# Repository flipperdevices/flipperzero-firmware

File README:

# About
This project is used to develop applications for stm32 - ST's ARM Cortex-M3(4) MCUs, using cmake, GCC, newlib (libc), STM32CubeMX package or ChibiOS.

Requirements:
* cmake >= 2.8
* GCC toolchain with newlib (optionally).
* STM32CubeMX package for STM32F1 or STM32F4 families.
Project contains:
* CMake common toolchain file, that configures cmake to use arm toolchain.
* CMake family-specific toolchain file, that configures family-specific parameters.
* CMake modules to find and configure CMSIS ans STM32HAL components.
* CMake modules to find and configure ChibiOS components.
* CMake project template.
* Example projects:
  * stm32-blinky - blink LED using timers and PWM.
  * stm32-newlib - show date using uart and libc functions from newlib
  * stm32-chibios - blink led using ChibiOS/NIL

# Usage
First of all you need to configure toolchain and libraries, you can do this by editing gcc_stm32.cmake or (better way) pass it throught command line.
Variables for toolchain:
* TOOLCHAIN_PREFIX - where toolchain is located, **default**: /usr
* TARGET_TRIPLET - toolchain target triplet, **default**: arm-none-eabi
* STM32_CHIP - STM32 device code, e.g. STM32F407VG or STM32F103VG
* STM32_FAMILY - STM32 family (F0, F1, F4, etc.) currently, F1 and F4 family are supported. **Note:** If STM32_CHIP variable is set, STM32_FAMILY is optional.
* STM32Cube_DIR - path to STM32CubeMX directory **default**: /opt/STM32Cube_FW_F1_V1.1.0 /opt/STM32Cube_FW_F4_V1.6.0

For using scripts you'll need to copy contents of cmake folder into cmake's modules path, or use CMAKE_MODULE_PATH variable. 
Template project can be found in stm32-template folder.

## Configure
Common usage:

 ```cmake -DSTM32_CHIP=<chip> -DCMAKE_TOOLCHAIN_FILE=<path_to_gcc_stm32.cmake> -DCMAKE_BUILD_TYPE=Debug <path_to_source_dir>```

Where <chip> - stm32 chip name (e.g. STM32F100C8, STM32F407IG). 
This command will generate Makefile for project.
Scripts will try to detected chip parameters (type, flash/ram size) from chip name. 
You can set this parameters directly using following cmake variables:
* STM32_CHIP_TYPE - family-depended chip type. Global variable STM32_CHIP_TYPES contains list of valid types for current family
* STM32_FLASH_SIZE - chip flash size (e.g. 64K)
* STM32_RAM_SIZE - chip RAM size (e.g. 4K)

For using with Eclipse CDT:

 ```cmake -DSTM32_CHIP=<chip> -DCMAKE_TOOLCHAIN_FILE=<path_to_gcc_stm32.cmake> -DCMAKE_BUILD_TYPE=Debug -G "Eclipse CDT4 - Unix Makefiles" <path_to_source_dir>```

For release build:

 ```cmake -DSTM32_CHIP=<chip> -DCMAKE_TOOLCHAIN_FILE=<path_to_gcc_stm32.cmake> -DCMAKE_BUILD_TYPE=Release <path_to_source_dir>```

## Build

 ```make`
 
To build .hex:

 ```make <project name>.hex```
 
or .bin:

 ```make <project name>.bin```

## Linker script variables
Next cmake variables are useful for linker tuning:
* STM32_LINKER_SCRIPT - Path to custom linker script. You can use cmake variables (listed below) in itd.
* STM32_FLASH_ORIGIN - Start address of flash (**default**: 0x08000000)
* STM32_RAM_ORIGIN - Start address of RAM (**default**: 0x20000000)
* STM32_CCRAM_ORIGIN - Start address of Core-Coupled RAM (only for F4 family) (**default**: 0x10000000)
* STM32_FLASH_SIZE - Flash size (**default**: from chip name)
* STM32_RAM_SIZE - RAM size (**default**: from chip name)
* STM32_CCRAM_SIZE - Core-Coupled RAM size (only for F4 family) (**default**: 64 KiB)
* STM32_MIN_STACK_SIZE - Minimum stack size for error detection at link-time (**default**: 512 bytes)
* STM32_MIN_HEAP_SIZE - Minimum heap size for error detection at link-time (**default**: 0 bytes)

## Useful cmake macros
* STM32_GET_CHIP_TYPE(CHIP CHIP_TYPE) - gets chip type from chip name.
* STM32_GET_CHIP_PARAMETERS(CHIP FLASH_SIZE RAM_SIZE) - gets chip ram/flash size from chip name.
* STM32_SET_CHIP_DEFINITIONS(TARGET CHIP_TYPE) - sets chip family and type-specific compiler flags for target.
* STM32_SET_FLASH_PARAMS(TARGET ...) - sets chip flash/ram parameters for targer.
* STM32_SET_TARGET_PROPERTIES(TARGET) - sets all needed parameters and compiler flags for target. 
* STM32_GENERATE_LIBRARIES(NAME SOURCES LIBRARIES) - generates libraries for all chip types in family. Resulting libraries stored in LIBRARIES and have names in ${NAME}_${FAMILY}_${CHIP_TYPE} format.

## ChibiOS Support
This projects also supports ChibiOS v3.x.x (both nil and rt kernels). 
CMake modules for ChibiOS can find specified ChibiOS components using COMPONENTS directive. 
See project stm32-chibios for example usage.

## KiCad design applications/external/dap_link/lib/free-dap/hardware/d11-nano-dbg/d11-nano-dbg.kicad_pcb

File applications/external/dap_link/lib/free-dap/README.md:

# Free-DAP

This is a free and open implementation of the CMSIS-DAP debugger firmware.

Both SWD and JTAG protocols are supported. However JTAG was not well tested due to lack of
good targets. If you have any issues with it - let me know and I'll try to help.

## Platform requirements

To create a CMSIS-DAP compliant debugger, your platform must:
 * Implement USB HID (and raw bulk for CMSIS-DAP v2) device able to receive and send arbitrary payloads
 * Provide configuration file dap_config.h with definitions for hardware-dependent calls
 * Call dap_init() at the initialization time
 * Call dap_process_request() for every received request and send the response back

## CMSIS-DAP version support

Free-DAP library itself is protocol agnostic and implementation of the specific version
of the CMSIS-DAP protocol (v1 or v2) is up to the individual platforms.

Currently RP2040 and SAM D11 implementaitons were updated to support CMSIS-DAP v2.
Other platforms would be updated if requested or needed by me.

## Configuration

For complete list of settings see one of the existing configuration file, they are
pretty obvious.

To configure clock frequency you need to specify two parameters:
  * DAP_CONFIG_DELAY_CONSTANT - clock timing constant. This constant can be determined
    by calling dap_clock_test() with varying parameter value and measuring the frequency
    on the SWCLK pin. Delay constant value is the value of the parameter at which
    output frequency equals to 1 kHz.
  * DAP_CONFIG_FAST_CLOCK - threshold for switching to fast clock routines. This value
    defines the frequency, at which more optimal pin manipulation functions are used.
    This is the frequency produced by dap_clock_test(1) on the SWCLK pin.
    You can also measure maximum achievable frequency on your platform by calling dap_clock_test(0).

Your configuration file will need to define the following pin manipulation functions:

 * DAP_CONFIG_SWCLK_TCK_write()
 * DAP_CONFIG_SWDIO_TMS_write()
 * DAP_CONFIG_TDO_write()
 * DAP_CONFIG_nTRST_write()
 * DAP_CONFIG_nRESET_write()
 * DAP_CONFIG_SWCLK_TCK_read()
 * DAP_CONFIG_SWDIO_TMS_read()
 * DAP_CONFIG_TDI_read()
 * DAP_CONFIG_TDO_read()
 * DAP_CONFIG_nTRST_read()
 * DAP_CONFIG_nRESET_read()
 * DAP_CONFIG_SWCLK_TCK_set()
 * DAP_CONFIG_SWCLK_TCK_clr()
 * DAP_CONFIG_SWDIO_TMS_in()
 * DAP_CONFIG_SWDIO_TMS_out()

Note that all pin manipulation functions are required even if one of the interfaces (JTAG or SWD) is not enabled.

Additionally configuration file must provide basic initialization and control functions:

 * DAP_CONFIG_SETUP()
 * DAP_CONFIG_DISCONNECT()
 * DAP_CONFIG_CONNECT_SWD()
 * DAP_CONFIG_CONNECT_JTAG()
 * DAP_CONFIG_LED()
 * DAP_CONFIG_DELAY()

## Tools

A complete RP2040 build requres bin2uf2 utility to generate UF2 file suitable for the RP2040 MSC bootloader.
This utility can be downloded [here](https://github.com/ataradov/tools/tree/master/bin2uf2).

## Binaries

Generally there are no pre-built binaries due to effort required to maintain
them and low potential benefit because of custom hardware requirement.

For RP2040 and Raspberry Pi Pico board specifically there is a binary, since
it is a standard and a widely available board that has a nonvolatile bootloader.

The UF2 file is located [here](bin/free_dap_rp2040.uf2). Simply boot into
a BootROM MSC mode and copy that file to the drive.

I will try to do my best to keep this binary in sync with the code updates, but
it is a manual process, so I may forget. Let me know if you have any issues.

The pins used are as follows:

| GPIO | Function |
|:---:|:---|
| 11 | SWCLK/TCK |
| 12 | SWDIO/TMS |
| 13 | TDI |
| 14 | TDO |
| 15 | nRESET |
| 0 | VCP TX |
| 1 | VCP RX |
| 2 | VCP Status |
| 25 (LED) | DAP Status |

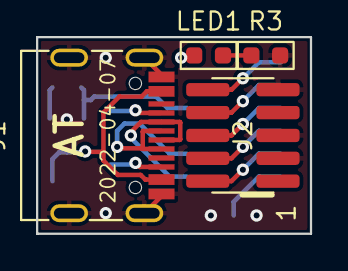
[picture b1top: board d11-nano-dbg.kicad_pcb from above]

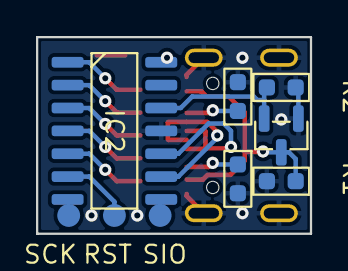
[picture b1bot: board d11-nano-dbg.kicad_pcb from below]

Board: 2 copper layers, 15.2 x 10.9 mm, 13 parts (9 on the bottom side), 17 nets.

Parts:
C1, C2: 1uF; 0603
IC1: SC662K-3.3; SOT-23
IC2: ATSAMD11C; SOIC-14
J1: USB-C
J2: Conn-5x2; Header-5x2-1.27mm-SMD
LED1: Orange; 0603
R1, R2: 5.1K; 0603
R3: 20K; 0603
TP1: SCK; TestPoint-1.27mm-SMD
TP2: RST; TestPoint-1.27mm-SMD
TP3: SIO; TestPoint-1.27mm-SMD

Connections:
+3V3: C2.2, IC1.2 (OUT), IC2.12 (VDD)
/DAP_STATUS: IC2.14 (PA4), LED1.1 (A)
/DBG_RESET: IC2.6 (PA28/RST), TP2.1
/DBG_SWCLK: IC2.7 (PA30/SCK), TP1.1
/DBG_SWDIO: IC2.8 (PA31/SIO), TP3.1
/RESET: IC2.1 (PA5), J2.10
/SWCLK/TCK: IC2.4 (PA14), J2.4
/SWDIO/TMS: IC2.5 (PA15), J2.2
/TDI: IC2.2 (PA8), J2.8
/TDO: IC2.3 (PA9), J2.6
/USB_DM: IC2.9 (PA24/DM), J1.D-1 (D-), J1.D-2 (D-)
/USB_DP: IC2.10 (PA25/DP), J1.D+1 (D+), J1.D+2 (D+)
GND: C1.1, C2.1, IC1.1 (GND), IC2.11 (GND), J1.GND1 (GND), J1.GND2 (GND), J1.S1, J1.S2, J1.S3, J1.S4, J2.3, J2.5, J2.9, R1.1, R2.1, R3.1
unnamed: J1.CC1, R2.2
unnamed: J1.CC2, R1.2
unnamed: LED1.2 (K), R3.2
VBUS: C1.2, IC1.3 (IN), J1.VBUS1 (VBUS), J1.VBUS2 (VBUS)

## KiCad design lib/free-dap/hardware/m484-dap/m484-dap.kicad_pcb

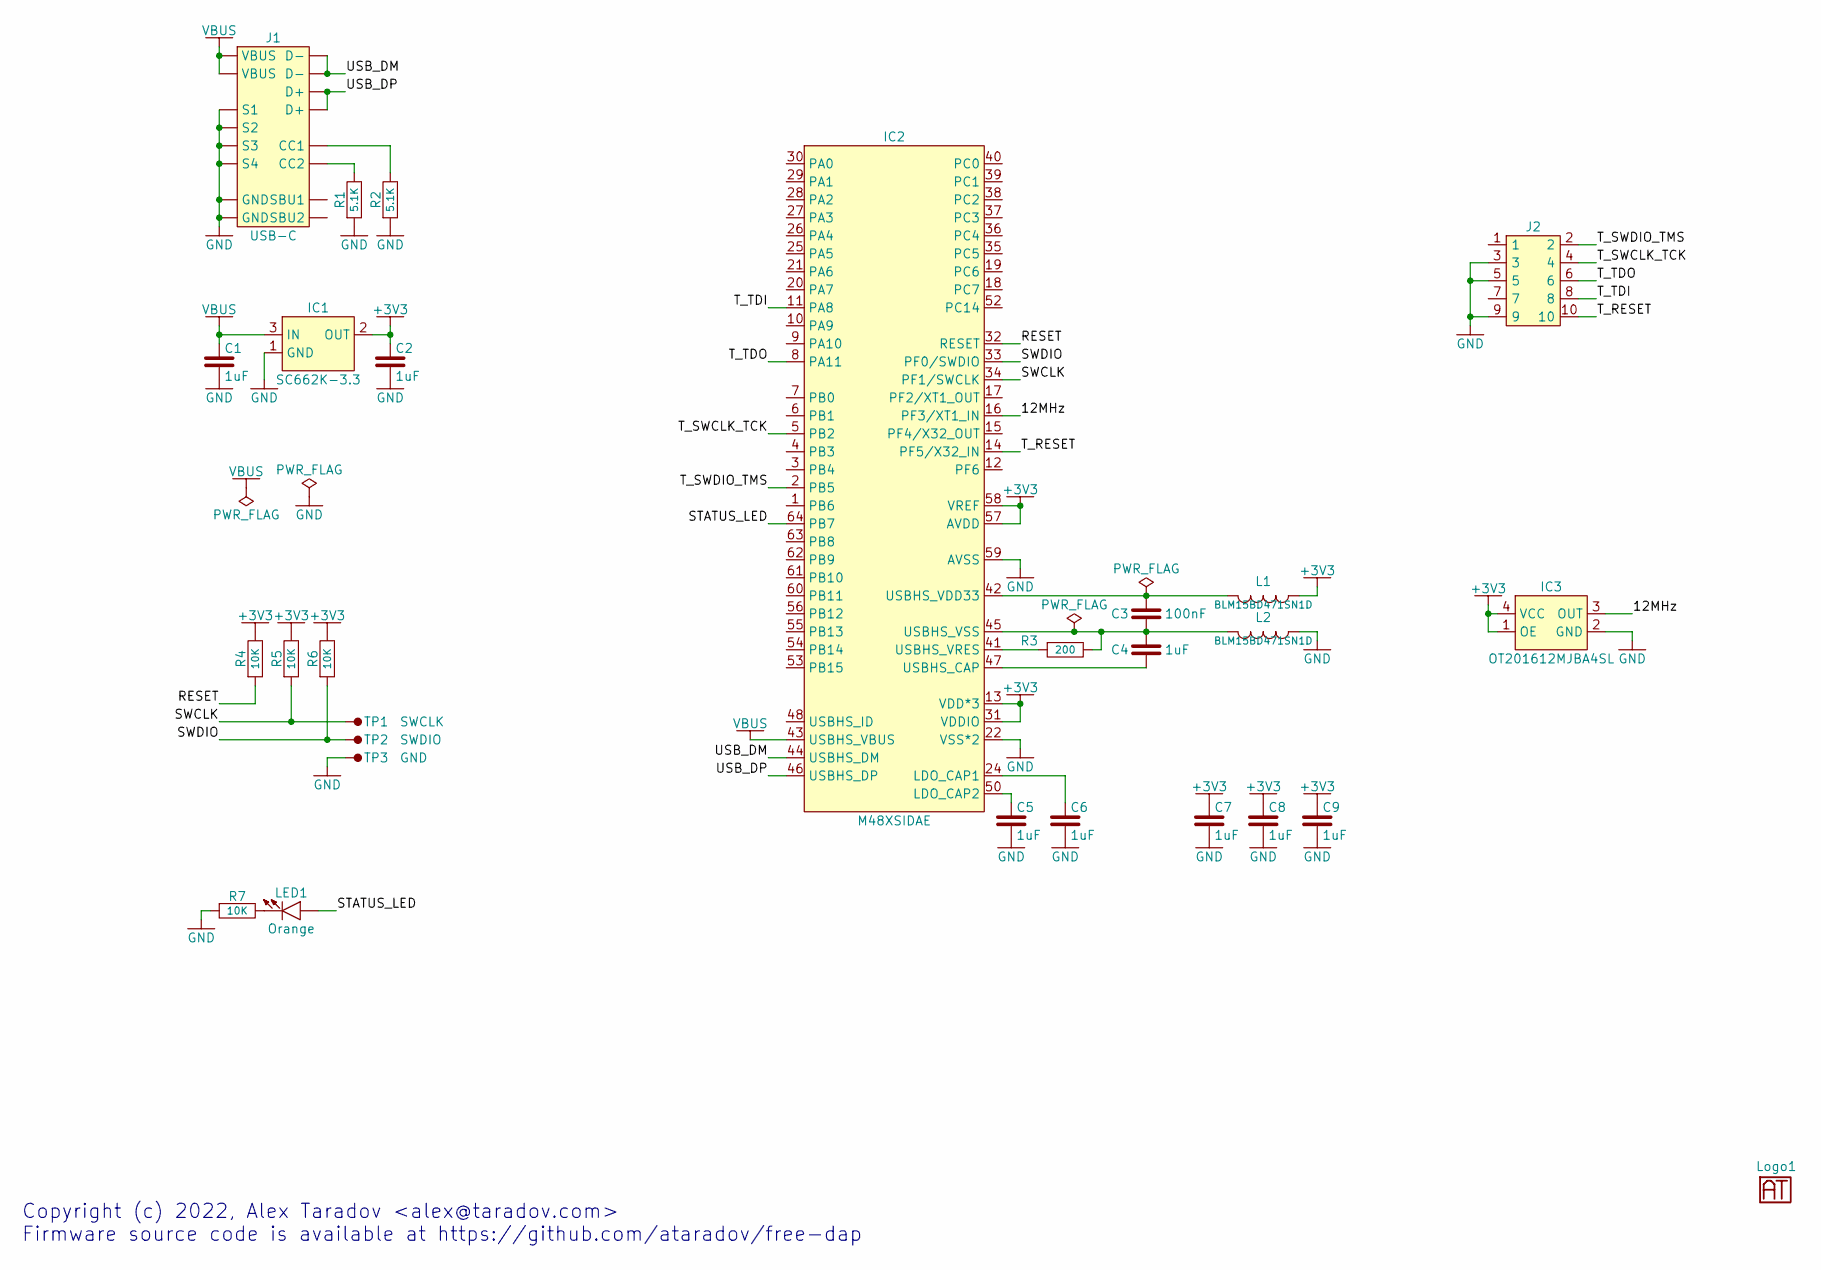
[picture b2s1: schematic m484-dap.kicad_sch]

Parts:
C1, C2, C7, C8, C9: 1uF; 0603
C3: 100nF; 0402
C4, C5, C6: 1uF; 0402
IC1: SC662K-3.3; SOT-23
IC2: M48XSIDAE; TQFP-64-0.4mm
IC3: OT201612MJBA4SL; SMD2016-4P
J1: USB-C
J2: Conn-5x2; Header-5x2-1.27mm
L1, L2: BLM15BD471SN1D; 0402
LED1: Orange; 0603
Logo1: Logo; Logo-Small
R1, R2: 5.1K; 0603
R3: 200; 0402
R4, R5, R6, R7: 10K; 0603
TP1: SWCLK; TestPoint-1.27mm-Small
TP2: SWDIO; TestPoint-1.27mm-Small
TP3: GND; TestPoint-1.27mm-Small

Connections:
+3V3: C2.2, C7.2, C8.2, C9.2, IC1.2 (OUT), IC2.13 (VDD*3), IC2.23 (VDD), IC2.31 (VDDIO), IC2.51 (VDD), IC2.57 (AVDD), IC2.58 (VREF), IC3.1 (OE), IC3.4 (VCC), L1.2, R4.2, R5.2, R6.2
/12MHz: IC2.16 (PF3/XT1_IN), IC3.3 (OUT)
/RESET: IC2.32 (RESET), R4.1
/STATUS_LED: IC2.64 (PB7), LED1.1 (A)
/SWCLK: IC2.34 (PF1/SWCLK), R5.1, TP1.1
/SWDIO: IC2.33 (PF0/SWDIO), R6.1, TP2.1
/T_RESET: IC2.14 (PF5/X32_IN), J2.10
/T_SWCLK_TCK: IC2.5 (PB2), J2.4
/T_SWDIO_TMS: IC2.2 (PB5), J2.2
/T_TDI: IC2.11 (PA8), J2.8
/T_TDO: IC2.8 (PA11), J2.6
/USB_DM: IC2.44 (USBHS_DM), J1.D-1 (D-), J1.D-2 (D-)
/USB_DP: IC2.46 (USBHS_DP), J1.D+1 (D+), J1.D+2 (D+)
GND: C1.1, C2.1, C5.1, C6.1, C7.1, C8.1, C9.1, IC1.1 (GND), IC2.22 (VSS*2), IC2.49 (VSS), IC2.59 (AVSS), IC3.2 (GND), J1.GND1 (GND), J1.GND2 (GND), J1.S1, J1.S2, J1.S3, J1.S4, J2.3, J2.5, J2.9, L2.2, R1.1, R2.1, R7.1, TP3.1
unnamed: C3.1, C4.2, IC2.45 (USBHS_VSS), L2.1, R3.2
unnamed: C3.2, IC2.42 (USBHS_VDD33), L1.1
unnamed: C4.1, IC2.47 (USBHS_CAP)
unnamed: C5.2, IC2.50 (LDO_CAP2)
unnamed: C6.2, IC2.24 (LDO_CAP1)
unnamed: IC2.41 (USBHS_VRES), R3.1
unnamed: J1.CC1, R2.2
unnamed: J1.CC2, R1.2
unnamed: LED1.2 (K), R7.2
VBUS: C1.2, IC1.3 (IN), IC2.43 (USBHS_VBUS), J1.VBUS1 (VBUS), J1.VBUS2 (VBUS)

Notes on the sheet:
Copyright (c) 2022, Alex Taradov <alex@taradov.com> Firmware source code is available at https://github.com/ataradov/free-dap

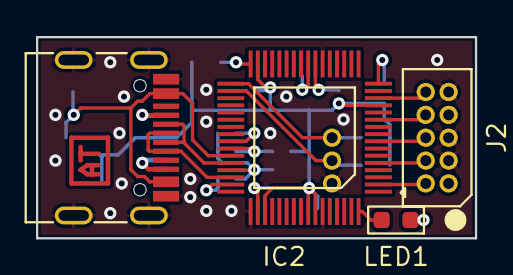
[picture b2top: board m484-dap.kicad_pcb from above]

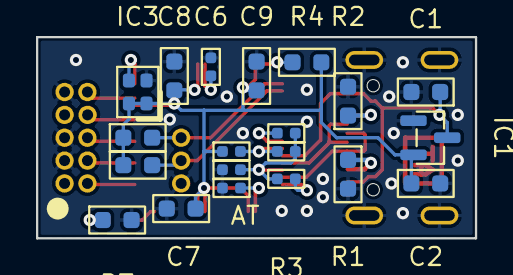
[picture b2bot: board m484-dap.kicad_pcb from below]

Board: 2 copper layers, 24.4 x 11.2 mm, 28 parts (20 on the bottom side), 24 nets.

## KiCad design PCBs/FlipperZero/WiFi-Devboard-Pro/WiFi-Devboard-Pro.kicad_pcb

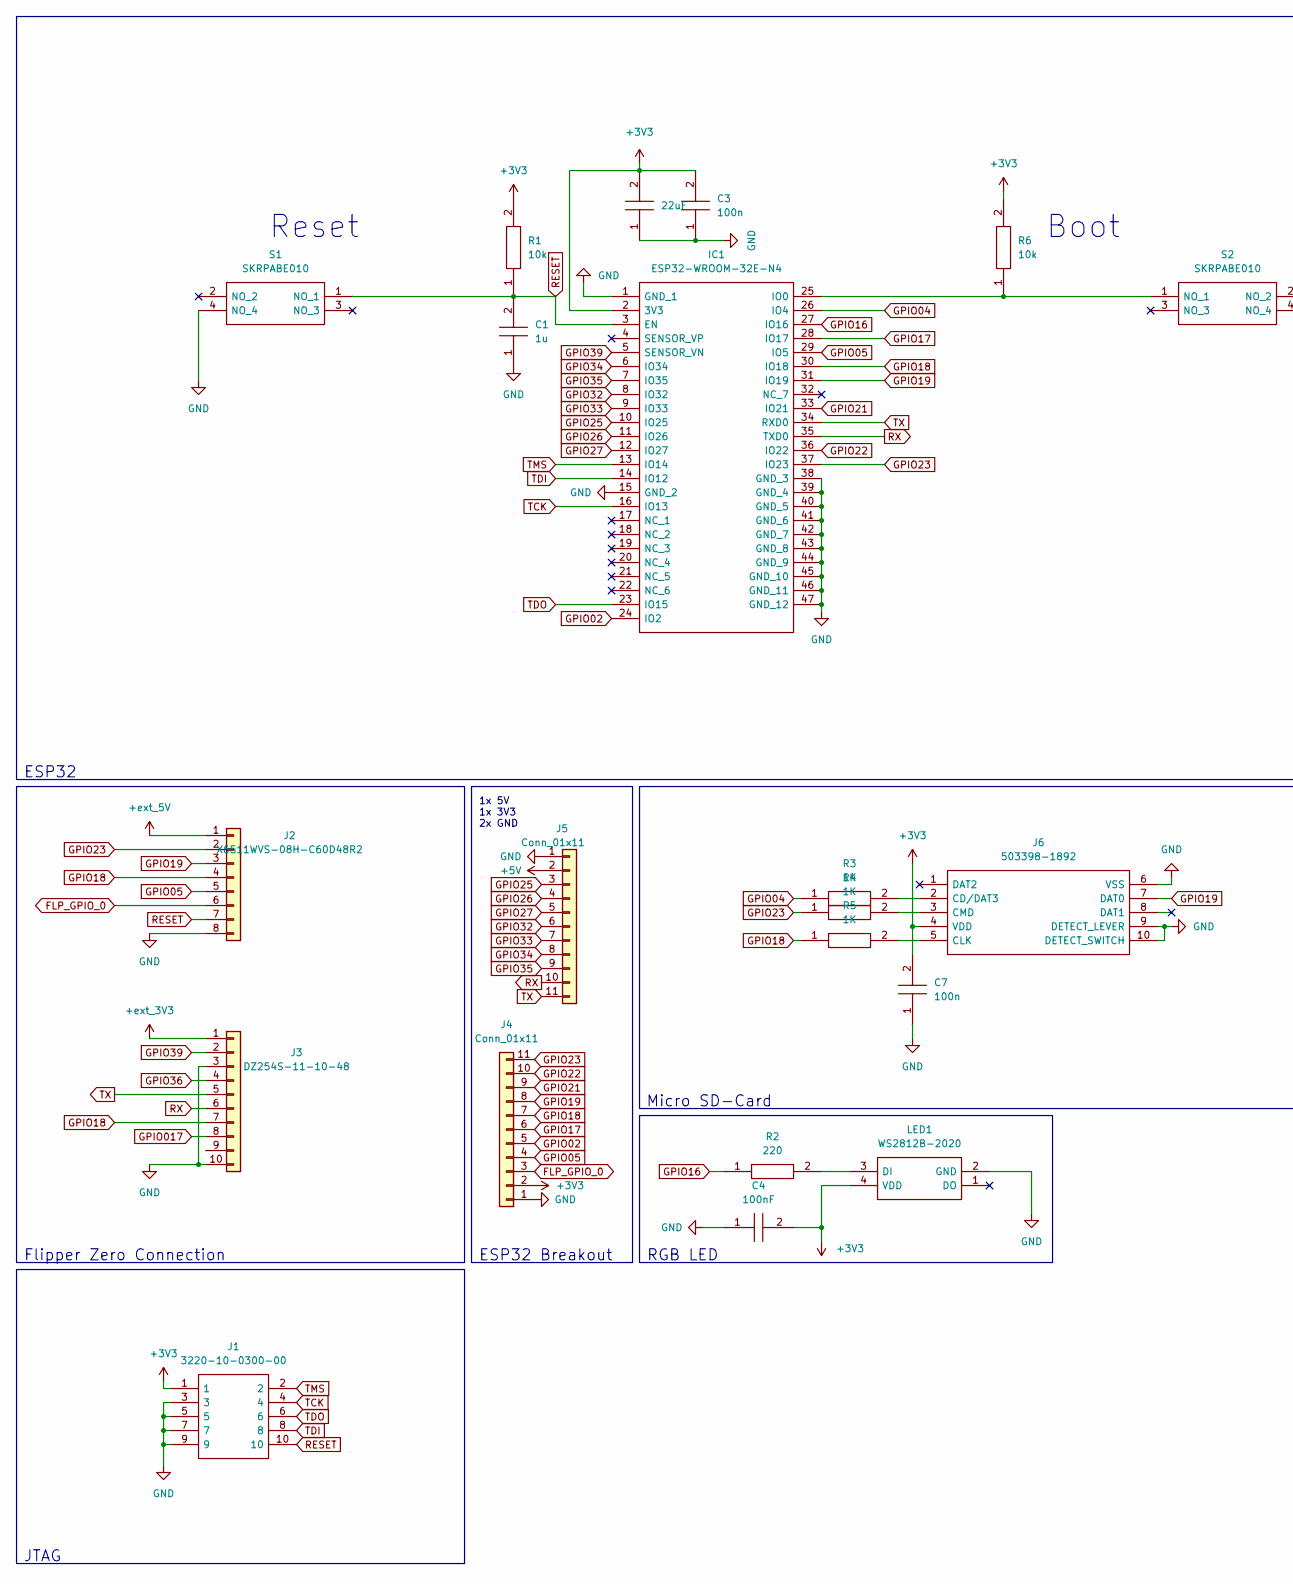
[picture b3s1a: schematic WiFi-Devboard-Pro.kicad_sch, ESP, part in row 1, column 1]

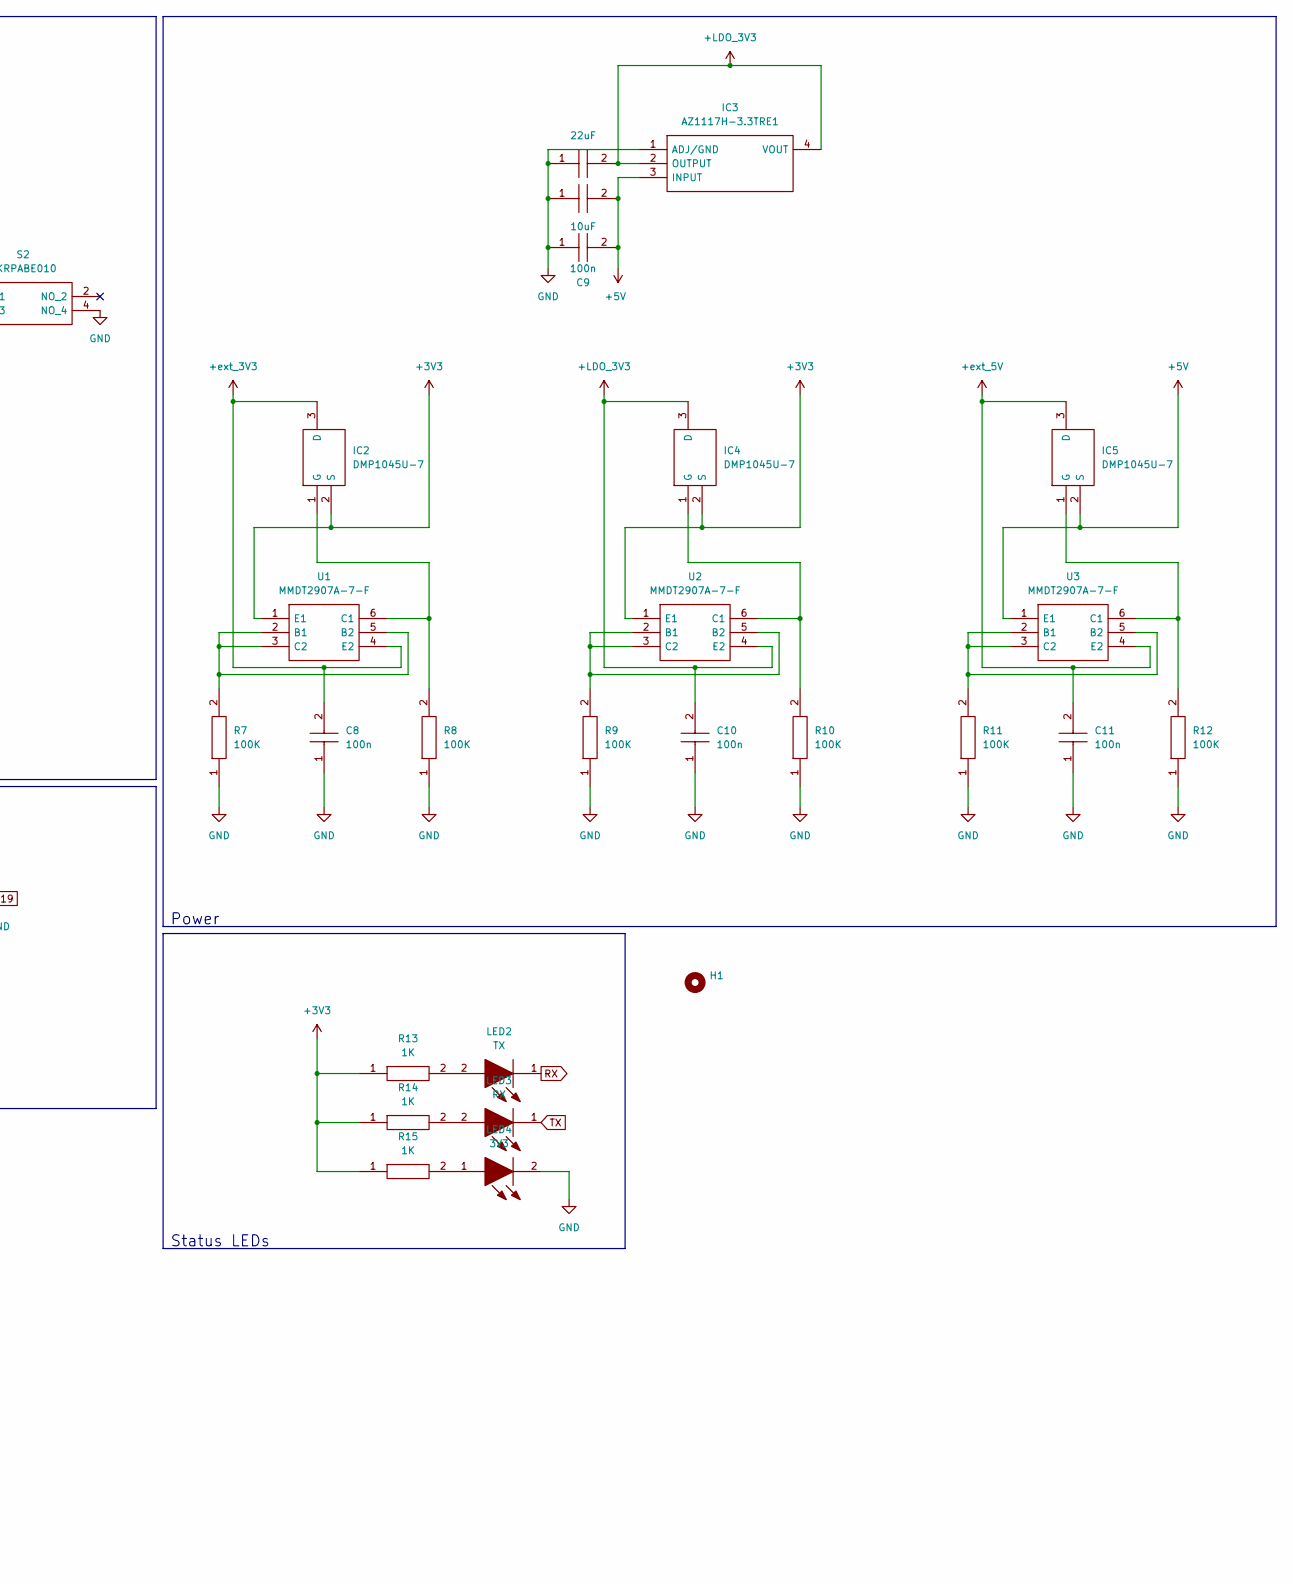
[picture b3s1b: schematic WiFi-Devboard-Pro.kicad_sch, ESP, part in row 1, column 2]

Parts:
C1: 1u; CAPC1005X60N; Manufacturer_Part_Number CL05A105KA5NQNC; Mouser Part Number 187-CL05A105KA5NQNC
C2, C5: 22uF; CAPC1005X80N; Manufacturer_Part_Number CM05X5R226M06AH080; Mouser Part Number 346-CM05X5R226M6AH80
C3, C7, C8, C9, C10, C11: 100n; CAPC1005X55N; Manufacturer_Part_Number CL05B104KO5NNNC; Mouser Part Number 187-CL05B104KO5NNNC
C4: 100nF; CAPC1005X55N; Manufacturer_Part_Number CC0402KRX7R7BB104; Mouser Part Number 603-CC402KRX7R7BB104
C6: 10uF; CAPC1005X70N; Manufacturer_Part_Number CL05A106MQ5NUNC; Mouser Part Number 187-CL05A106MQ5NUNC
H1: (no value)
IC1: ESP32-WROOM-32E-N4; ESP32WROOM32EN4; Manufacturer_Part_Number ESP32-WROOM-32E-N4; Mouser Part Number 356-ESP32WRM32E132PH
IC2, IC4, IC5: DMP1045U-7; SOT96P240X120-3N; Manufacturer_Part_Number DMP1045U-7; Mouser Part Number 621-DMP1045U-7
IC3: AZ1117H-3.3TRE1; SOT230P700X180-4N; Manufacturer_Part_Number AZ1117H-3.3TRE1; Mouser Part Number 621-AZ1117H-3.3TRE1
J1: 3220-10-0300-00; 322010030000; Manufacturer_Part_Number 3220-10-0300-00
J2: X6511WVS-08H-C60D48R2; HUSRSP8W66P254_2000X250X850P; Manufacturer_Part_Number X6511WVS-08H-C60D48R2
J3: DZ254S-11-10-48; HUSRSP10W66P254_2500X250X850P; Manufacturer_Part_Number DZ254S-11-10-48
J4, J5: Conn_01x11; PinHeader_1x11_P2.54mm_Vertical
J6: 503398-1892; Manufacturer_Part_Number 503398-1892; Mouser Part Number 538-503398-1892
LED1: WS2812B-2020; WS2812B2020; Manufacturer_Part_Number WS2812B-2020
LED2: TX; LEDC1608X50N; Manufacturer_Part_Number 19-217/Y5C-AP1Q2/3T; Mouser Part Number 638-19217Y5CAP1Q23T
LED3: RX; LEDC1608X50N; Manufacturer_Part_Number 19-217/Y5C-AP1Q2/3T; Mouser Part Number 638-19217Y5CAP1Q23T
LED4: 3V3; 19217R6CAL1M2VY3T; Manufacturer_Part_Number 19-217/R6C-AL1M2VY/3T
R1, R6: 10k; RESC1005X40N; Manufacturer_Part_Number RC0402FR-0710KL; Mouser Part Number 603-RC0402FR-0710KL
R2: 220; RESC1005X40N; Manufacturer_Part_Number RC0402FR-07220RL; Mouser Part Number 603-RC0402FR-07220RL
R3, R4, R5, R13, R14, R15: 1K; RESC1005X40N; Manufacturer_Part_Number RC0402FR-071KL; Mouser Part Number 603-RC0402FR-071KL
R7, R8, R9, R10, R11, R12: 100K; RESC1005X40N; Manufacturer_Part_Number RC0402FR-07100KL; Mouser Part Number 603-RC0402FR-07100KL
S1, S2: SKRPABE010; Manufacturer_Part_Number SKRPABE010; Mouser Part Number 688-SKRPAB
U1, U2, U3: MMDT2907A-7-F; SOT65P210X110-6N; Manufacturer_Part_Number MMDT2907A-7-F; Mouser Part Number 621-MMDT2907A-F

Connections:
+3V3: C2.2, C3.2, C4.2, C7.2, IC1.2 (3V3), IC2.2 (S), IC4.2 (S), J1.1, J4.2, J6.4 (VDD), LED1.4 (VDD), R1.2, R6.2, R13.1, R14.1, R15.1, U1.1 (E1), U2.1 (E1)
+5V: C6.2, C9.2, IC3.3 (INPUT), IC5.2 (S), J5.2, U3.1 (E1)
+LDO_3V3: C5.2, C10.2, IC3.2 (OUTPUT), IC3.4 (VOUT), IC4.3 (D), U2.4 (E2)
+ext_3V3: C8.2, IC2.3 (D), J3.1, U1.4 (E2)
+ext_5V: C11.2, IC5.3 (D), J2.1, U3.4 (E2)
FLP_GPIO_0: J2.6, J4.3
GND: C1.1, C2.1, C3.1, C4.1, C5.1, C6.1, C7.1, C8.1, C9.1, C10.1, C11.1, IC1.1 (GND_1), IC1.15 (GND_2), IC1.38 (GND_3), IC1.39 (GND_4), IC1.40 (GND_5), IC1.41 (GND_6), IC1.42 (GND_7), IC1.43 (GND_8), IC1.44 (GND_9), IC1.45 (GND_10), IC1.46 (GND_11), IC1.47 (GND_12), IC3.1 (ADJ/GND), J1.3, J1.5, J1.7, J1.9, J2.8, J3.3, J3.10, J4.1, J5.1, J6.6 (VSS), J6.9 (DETECT_LEVER), J6.10 (DETECT_SWITCH), LED1.2 (GND), LED4.2, R7.1, R8.1, R9.1, R10.1, R11.1, R12.1, S1.4 (NO), S2.4 (NO)
GPIO02: IC1.24 (IO2), J4.5
GPIO04: IC1.26 (IO4), R3.1
GPIO05: IC1.29 (IO5), J2.5, J4.4
GPIO16: IC1.27 (IO16), R2.1
GPIO17: IC1.28 (IO17), J4.6
GPIO017: J3.8
GPIO18: IC1.30 (IO18), J2.4, J3.7, J4.7, R5.1
GPIO19: IC1.31 (IO19), J2.3, J4.8, J6.7 (DAT0)
GPIO21: IC1.33 (IO21), J4.9
GPIO22: IC1.36 (IO22), J4.10
GPIO23: IC1.37 (IO23), J2.2, J4.11, R4.1
GPIO25: IC1.10 (IO25), J5.3
GPIO26: IC1.11 (IO26), J5.4
GPIO27: IC1.12 (IO27), J5.5
GPIO32: IC1.8 (IO32), J5.6
GPIO33: IC1.9 (IO33), J5.7
GPIO34: IC1.6 (IO34), J5.8
GPIO35: IC1.7 (IO35), J5.9
GPIO36: J3.4
GPIO39: IC1.5 (SENSOR_VN), J3.2
unnamed: IC1.25 (IO0), R6.1, S2.1 (NO)
unnamed: IC2.1 (G), R8.2, U1.6 (C1)
unnamed: IC4.1 (G), R10.2, U2.6 (C1)
unnamed: IC5.1 (G), R12.2, U3.6 (C1)
unnamed: J6.2 (CD/DAT3), R3.2
unnamed: J6.3 (CMD), R4.2
unnamed: J6.5 (CLK), R5.2
unnamed: LED1.3 (DI), R2.2
unnamed: LED2.2, R13.2
unnamed: LED3.2, R14.2
unnamed: LED4.1, R15.2
unnamed: R7.2, U1.2 (B1), U1.3 (C2), U1.5 (B2)
unnamed: R9.2, U2.2 (B1), U2.3 (C2), U2.5 (B2)
unnamed: R11.2, U3.2 (B1), U3.3 (C2), U3.5 (B2)
RESET: C1.2, IC1.3 (EN), J1.10, J2.7, R1.1, S1.1 (NO)
RX: IC1.35 (TXD0), J3.6, J5.10, LED2.1
TCK: IC1.16 (IO13), J1.4
TDI: IC1.14 (IO12), J1.8
TDO: IC1.23 (IO15), J1.6
TMS: IC1.13 (IO14), J1.2
TX: IC1.34 (RXD0), J3.5, J5.11, LED3.1

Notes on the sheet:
ESP32 Breakout
Status LEDs
Boot
Micro SD-Card
1x 5V 1x 3V3 2x GND
Reset
Power
RGB LED
Flipper Zero Connection
ESP32
JTAG

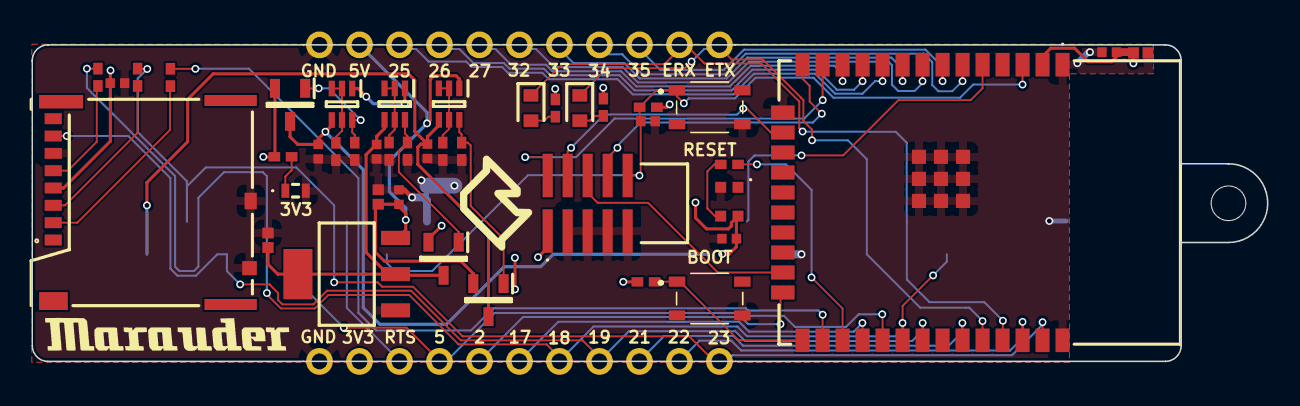
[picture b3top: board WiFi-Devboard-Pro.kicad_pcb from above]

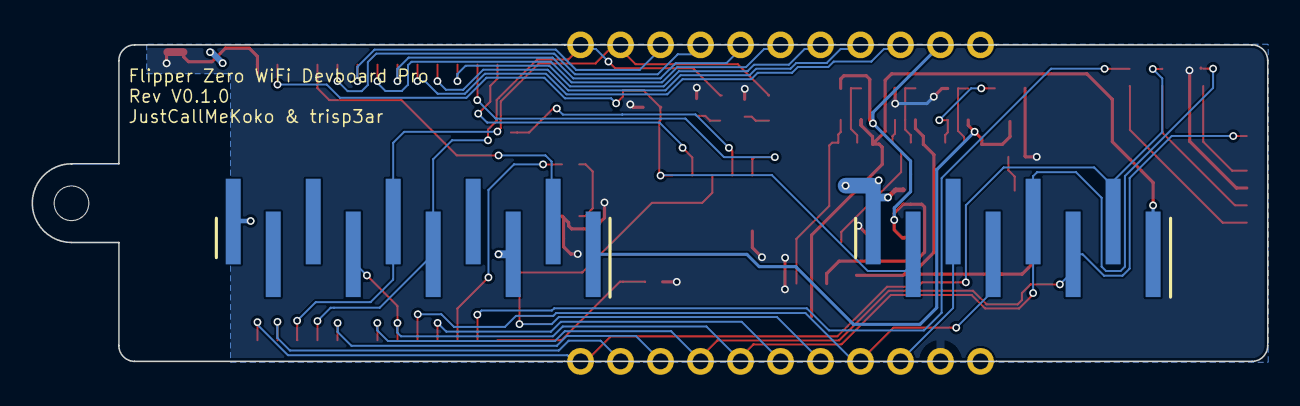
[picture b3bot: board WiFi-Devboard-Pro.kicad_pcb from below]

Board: 2 copper layers, 78.5 x 20.1 mm, 46 parts (2 on the bottom side), 46 nets.

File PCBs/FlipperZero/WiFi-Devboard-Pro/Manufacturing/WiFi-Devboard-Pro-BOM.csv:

"Id";"Designator";"Package";"Quantity";"Designation";"Supplier and ref";
1;"R10,R8,R12,R11,R9,R7";"RESC1005X40N";6;"100K";;;
2;"R15,R5,R4,R13,R14,R3";"RESC1005X40N";6;"1K";;;
3;"R6,R1";"RESC1005X40N";2;"10k";;;
4;"C7,C11,C3,C8,C9,C10";"CAPC1005X55N";6;"100n";;;
5;"IC2,IC4,IC5";"SOT96P240X120-3N";3;"DMP1045U-7";;;
6;"J4,J5";"PinHeader_1x11_P2.54mm_Vertical";2;"Conn_01x11";;;
7;"C2,C5";"CAPC1005X80N";2;"22uF";;;
8;"J6";"503398-1892";1;"503398-1892";;;
9;"LED1";"WS2812B2020";1;"WS2812B-2020";;;
10;"C6";"CAPC1005X70N";1;"10uF";;;
11;"IC1";"ESP32WROOM32EN4";1;"ESP32-WROOM-32E-N4";;;
12;"LED4";"19217R6CAL1M2VY3T";1;"3V3";;;
13;"R2";"RESC1005X40N";1;"220";;;
14;"J1";"322010030000";1;"3220-10-0300-00";;;
15;"LED2";"LEDC1608X50N";1;"TX";;;
16;"S2,S1";"SKRPABE010";2;"SKRPABE010";;;
17;"C4";"CAPC1005X55N";1;"100nF";;;
18;"IC3";"SOT230P700X180-4N";1;"AZ1117H-3.3TRE1";;;
19;"";"";1;"";;;
20;"U3,U2,U1";"SOT65P210X110-6N";3;"MMDT2907A-7-F";;;
21;"C1";"CAPC1005X60N";1;"1u";;;
22;"LED3";"LEDC1608X50N";1;"RX";;;
23;"J3";"HUSRSP10W66P254_2500X250X850P";1;"DZ254S-11-10-48";;;

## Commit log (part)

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2026-06-11 Implement language variable and settings entry
2026-06-12 Implement proper language switching
2026-06-12 Add i18n() wrappers to about.c
2026-06-13 i18n()-wrap Bluetooth settings
2026-06-13 i18n()-wrap clock settings
2026-06-13 Shorten i18n() placeholder string
2026-06-13 i18n()-wrap desktop settings
2026-06-14 Fix variable item lists not changing their strings when the language is changed
2026-06-14 Add infiles.list to gitignore
2026-06-14 First working version of the gettext extraction script
2026-06-15 Fix typo in SLIX-L unlock menu: "TommyBox" -> "TonieBox"
2026-06-24 Add integration test docs, discussion guidelines, and edit contribution guide
2026-06-25 Editorial changes to the integration test page
2026-06-25 Test cases fixed
2026-06-25 Backslashes removed
2026-06-25 Fix USB HID keyboard LED state reporting (#4162)
    Add missing OUT endpoint to USB HID keyboard interface so the host
    can send LED state reports (CapsLock, NumLock, ScrollLock) to the device.
    This makes furi_hal_hid_get_led_state() return the actual host LED state
    instead of always returning 0.
2026-06-25 NFC: Fix BusFault in Write to Initial Card
    mode_ctx is a union where write_ctx.tag_block overlaps with dict_attack_ctx.nested_nonce.nonces. In "Write to Initial Card" it causes mf_classic_poller_free calling free on a garbage pointer
2026-06-25 Storage: Dont send mount event if SD mounted at boot
2026-06-25 NFC: Fix sending 32+ byte ISO 15693-3 commands
2026-06-25 NFC: Fix stack buffer overflows in MFUL FAST_READ and DESFire file settings parsers
    mf_ultralight_listener.c: FAST_READ handler wrote page_cnt*4 bytes into
    a fixed pages[64] stack buffer without checking page_cnt <= 64. For tags
    with pages_total > 64 (NTAG215: 135, NTAG216: 231) a reader could trigger
    an overflow of up to 668 bytes. Fix: reject requests where page_cnt
    exceeds COUNT_OF(pages) with NAK.
    mf_desfire_i.c: additional_access_rights_len (a count) was validated
2026-06-25 NFC: ISO 15693-3 emulation READ_MULTI and GET_BLOCK_SECURITY fixes
2026-06-25 appmanifest: validate fap_version type; accept int, reject float
2026-06-25 Enable BQ25896 OTG on boot
2026-06-25 fix HID limits to support international keyboards
2026-06-25 add ja-JP keyboard
2026-06-25 build: disable -fstack-usage in production builds
    Disable -fstack-usage compiler flag that was enabled for stack analysis
    during the fix for issue #4332. Stack analysis is complete and should only
    be enabled during future stack usage investigations.
2026-06-25 refactor(boot): heap-allocate large FatFS structures in update path (#4332)
    Further optimization of boot update stack usage by moving large FatFS
    structures (FIL, FILINFO, path buffers) from stack to heap allocation.
    Refactored functions:
    1. flipper_update_get_manifest_path
    Before: ~1160 bytes (FIL + FILINFO + 256B buffer)
    After: ~50 bytes (pointers only)
2026-06-25 fix(boot): increase main thread stack to prevent overflow (#4332)
    - Increase stack size from 1024 → 2048 bytes (0x400 → 0x800)
    - Provides 1096 bytes headroom for boot update operations
    - Resolves potential overflow in flipper_update_process_manifest
    - Enable -fstack-usage for static stack analysis
2026-06-25 Fixes from ellyromanova
2026-06-25 fix(f6): skip radio stack updates
2026-06-25 fix(f6): restore rtc boot mode handling
2026-06-25 feat(subghz): expose developer region frequencies
2026-06-25 feat(nfc): add ndef write action for ntag21x
    Backport upstream PR #4372 with the URI, email, phone, text, and WPA2 Wi-Fi NDEF builders plus the NTAG213/215/216 write flow.
2026-06-25 Remove notion of the forum
2026-06-25 Update CODEOWNERS
2026-06-25 Fix general_test_cases.md symbol
2026-06-25 Fix general_test_cases.md again
2026-06-29 Fix links and other stuff
2026-06-29 Added Discussions to the readme
    - Added Discussions to the readme
    - Removed old roadmap from the readme
    - removed link to the discussion guideline fro contributing.md
2026-06-29 Link to the discussion guidelines added
2026-06-30 Update f18 API version
2026-06-30 fbt format
2026-06-30 Use actual spaces instead of empty buffer
2026-06-30 ci: make merge report workflow manual-only
2026-06-30 GUI: add canvas_buffer to public api
2026-06-30 GUI: add canvas_buffer to public api (f18)
2026-06-30 Fix condition for cleaning up dict attack resources
